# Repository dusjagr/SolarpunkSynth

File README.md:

# SolarpunkSynth 🌞🎹

A solar-powered synthesizer that creates experimental sounds, rhythmic patterns, and beats using minimal energy from the sun! This project embodies the spirit of solarpunk by combining sustainable energy with creative expression.

# Workshop Registration
https://sgmkcloud.ocloud.de/index.php/apps/forms/65qHgGpafZMqBaDL

## Description

The SolarpunkSynth is an ultra-low power consumption synthesizer that can be powered by:
- Silicon solar cells
- DIY DSSC (Dye-sensitized solar cells)
- Alternative power sources (mud batteries, potato power, coconut energy)
- Nearly depleted batteries (due to extremely low power requirements)

## Project Variants

This repository contains two versions of the SolarpunkSynth:

### 1. Original SolarpunkSynth
Located in [`/SolarPunkSynth`](./SolarPunkSynth)
- The original version of the solar-powered synthesizer
- Simple and elegant design
- Perfect for beginners and workshops
- Includes complete documentation and assembly instructions

### 2. Digilog Edition
Located in [`/SolarSynth_digilog`](./SolarSynth_digilog)
- Enhanced version with digital-inspired aesthetics
- Developed for the Digilog exhibition in Taipei, Taiwan
- Features artistic PCB design with custom graphics
- Same core functionality with a unique visual style

## Technical Details

The synthesizer is built around these key features:
- Based on hex-inverter chip (74HC14)
- Three interdependent oscillators coupled through piezo discs
- Ultra-low energy consumption (<0.5mA)
- Audio output via 3.5mm jack
- Organic, variable rhythms through unstable circuit states
- KiCad PCB design files included

### Technical Differences Between Variants

#### Original SolarpunkSynth
- Simple and robust circuit design
- Direct audio output from oscillator circuit
- Basic component selection for easy assembly
- Standard PCB layout optimized for functionality
- Ideal for workshops and educational purposes

#### Digilog Edition Enhancements
- Added MCP6002 dual op-amp for improved audio output buffering
- Enhanced signal conditioning with additional filtering capacitors
- Modified component values for better stability
- Custom footprint library optimized for artistic PCB layout
- Artistic PCB design with custom traces and visual elements
- ENIG finish recommended for superior aesthetic presentation
- Optional acrylic cover design for finished look and protection

### Schematic

You can also view the [minimal schematic as PDF](./SolarPunkSynth/instructions/DSSC_Synthminimal_schema.pdf).

## Assembly Instructions

### Original SolarpunkSynth

For the original SolarpunkSynth version:
- [Detailed Soldering Guide (PDF)](./SolarPunkSynth/instructions/SolderInstruction.pdf)
- [Soldering Guide (SVG)](./SolarPunkSynth/instructions/SolderInstruction.svg)
- **[Complete step-by-step assembly instructions](./SolarPunkSynth/README.md#detailed-step-by-step-assembly-instructions)** are included in the SolarPunkSynth README.md

### Digilog Edition

Instruction photos are available:

For the Digilog edition, additional documentation is available:
- [Leaflet Format Instructions (PDF)](./SolarSynth_digilog/instructions/SolarpunkSynth_SolderInstruction_leaflet.pdf)
- [Inside Pages (PDF)](./SolarSynth_digilog/instructions/SolarpunkSynth_SolderInstruction_leaflet_inside.pdf)
- [Outside Pages (PDF)](./SolarSynth_digilog/instructions/SolarpunkSynth_SolderInstruction_leaflet_outside.pdf)

## Repository Contents

- [`/SolarPunkSynth`](./SolarPunkSynth) - Original version KiCad files and documentation
  - [`/002_SolarPunkSynth_footprints.pretty`](./SolarPunkSynth/002_SolarPunkSynth_footprints.pretty) - Custom footprints for the PCB
  - [`/MASK`](./SolarPunkSynth/MASK) - PCB mask files and design assets
  - [`/instructions`](./SolarPunkSynth/instructions) - Assembly guides and schematics
  - [`/svg2shenzhen`](./SolarPunkSynth/svg2shenzhen) - SVG files for PCB artwork

- [`/SolarSynth_digilog`](./SolarSynth_digilog) - Digilog edition KiCad files
  - [`/3d_models`](./SolarSynth_digilog/3d_models) - 3D models of components
  - [`/DIY_pcb`](./SolarSynth_digilog/DIY_pcb) - DIY PCB patterns and masks for custom fabrication
  - [`/acrylicCover_digilog`](./SolarSynth_digilog/acrylicCover_digilog) - Design files for the optional acrylic protective cover
  - [`/gerber`](./SolarSynth_digilog/gerber) - Manufacturing files
  - [`/instructions`](./SolarSynth_digilog/instructions) - Enhanced assembly guides in multiple formats
  - [`/svg2shenzhen`](./SolarSynth_digilog/svg2shenzhen) - Custom PCB artwork files
  - [`BOM.ods`](./SolarSynth_digilog/BOM.ods) - Detailed bill of materials in OpenDocument Spreadsheet format

- [`/photos`](./photos) - Project photos and workshop documentation

## DIY PCB Fabrication

For those interested in creating their own PCBs at home or in makerspaces, the Digilog edition includes DIY PCB files:
- [`SolarSynth_MASK.png`](./SolarSynth_digilog/DIY_pcb/SolarSynth_MASK.png) - Printable mask pattern for toner transfer or photolithography
- [`SolarSynth_digilog_MASK.svg`](./SolarSynth_digilog/DIY_pcb/SolarSynth_digilog_MASK.svg) - Vector version of the mask for scaling and modifications

These files can be used with common DIY PCB fabrication methods like toner transfer, photolithography, or CNC milling.

## Acrylic Cover

The Digilog edition offers an optional aesthetic acrylic cover:
- [`acrylCover_digilog.dxf`](./SolarSynth_digilog/acrylicCover_digilog/acrylCover_digilog.dxf) - CAD file for laser cutting
- [`drawing.svg`](./SolarSynth_digilog/acrylicCover_digilog/drawing.svg) - Vector drawing for preview and modifications

The acrylic cover enhances the visual appeal while providing protection to the electronics.

## Workshop Information

A solar-powered synthesizer that creates experimental sounds, rhythmic patterns, and beats using minimal energy from the sun! This project embodies the spirit of solarpunk by combining sustainable energy with creative expression.

<figure>
  
  <figcaption><em>Impressions from the workshop at digilog, Taipei, February 2025</em></figcaption>
</figure>

This project is designed to be beginner-friendly and has been successfully taught in workshops across various locations including:
- Taipei, Taiwan (Digilog)
- Chiang Mai, Thailand
- Tokyo, Japan (FabCafe)

No prior electronics knowledge is required - just enthusiasm for experimental sounds and solar-powered creativity!

<figure>
  
  <figcaption><em>Photos from the SolarpunkSynth Workshop at Parang Cafe & Art Stay, Chiang Mai, Thailand</em></figcaption>
</figure>

## Credits

This circuit is a modified version of the StarvationSynth originally developed by Ralf Schreiber and Uwe Schüler. The current version was specifically developed by Marc Dusseiller (dusjagr) to support the exhibition "1,540,000nm DSSC" by Shih Wei-Chieh at FabCafe Tokyo.

### Tools Used
- [svg2shenzhen](https://github.com/badgeek/svg2shenzhen) - An Inkscape extension that converts SVG drawings to KiCad PCB layouts, allowing for artistic and unrestricted PCB designs with support for any kind of shapes, drill pads, and edge cuts. Special thanks to Budi Prakosa ([@badgeek](https://github.com/badgeek)) for creating this amazing tool!
- KiCad - PCB design software

## Links

- [Project Wiki](https://www.hackteria.org/wiki/SolarpunkSynth)
- [Hackteria Network](http://hackteria.org/)
- [SGMK](https://mechatronicart.ch/)
- [Bitwäscherei Hackerspace](https://bitwaescherei.ch/)

## License

This project is open hardware - feel free to modify and share!

This project is licensed under the CERN Open Hardware License Version 2 - Permissive (CERN-OHL-P v2). This means you are free to:
- Study
- Modify
- Make
- Distribute

without any obligation to share your changes or modifications.

For more details, see the [LICENSE](./LICENSE) file.

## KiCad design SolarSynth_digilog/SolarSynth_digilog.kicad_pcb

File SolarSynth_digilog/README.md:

# SolarpunkSynth Digilog Edition

This is the Digilog edition of the SolarpunkSynth, specially developed for the Digilog exhibition in Taipei, Taiwan. This version features an artistic PCB design while maintaining the core functionality of the original SolarpunkSynth.

## Features
- Enhanced PCB design with digital-inspired aesthetics
- Artistic circuit traces and visual elements
- Exhibition-ready presentation
- Improved audio output stage with op-amp buffer
- Ultra-low power consumption (<0.5mA)

## Technical Enhancements
- Added MCP6002 dual op-amp for better audio output buffering
- Enhanced signal conditioning with additional filtering
- Modified component values for improved stability
- Custom footprint library optimized for artistic PCB layout
- Polarized capacitors for better power filtering

## Directory Contents
- `/3d_models/` - 3D models of components for visualization
- `/gerber/` - Manufacturing files for PCB production
- `/svg2shenzhen/` - Custom PCB artwork files

## Exhibition History
- Digilog Exhibition, Taipei, Taiwan
- Part of the exploration of digital aesthetics in analog circuits
- Demonstrates the intersection of art and technology

## Technical Specifications
- Based on 74HC14 hex-inverter chip
- Three coupled oscillators using piezo discs
- MCP6002 dual op-amp for audio buffering
- Solar-powered operation
- 3.5mm audio output
- Artistic PCB design with custom traces

## PCB Design Process
The artistic PCB design was created using:
- [svg2shenzhen](https://github.com/badgeek/svg2shenzhen) - An Inkscape extension that transforms SVG artwork into KiCad PCB layouts, enabling complete creative freedom in PCB design with support for any shape and custom drill sizes
- Custom artwork designed specifically for the Digilog exhibition
- Careful consideration of both aesthetic and functional aspects

## Manufacturing Notes
- Gerber files are provided in the `/gerber/` directory
- PCB specifications:
  - 2-layer board
  - Custom silkscreen artwork
  - ENIG finish recommended for best aesthetic results

## Assembly
While the assembly process is similar to the original SolarpunkSynth, this version includes additional components:
1. MCP6002 dual op-amp in DFN-8 package
2. Additional filtering capacitors
3. Modified resistor values for the op-amp stage

Please refer to the schematic for detailed component values and connections.

## License
This project is licensed under the CERN Open Hardware License Version 2 - Permissive (CERN-OHL-P v2).

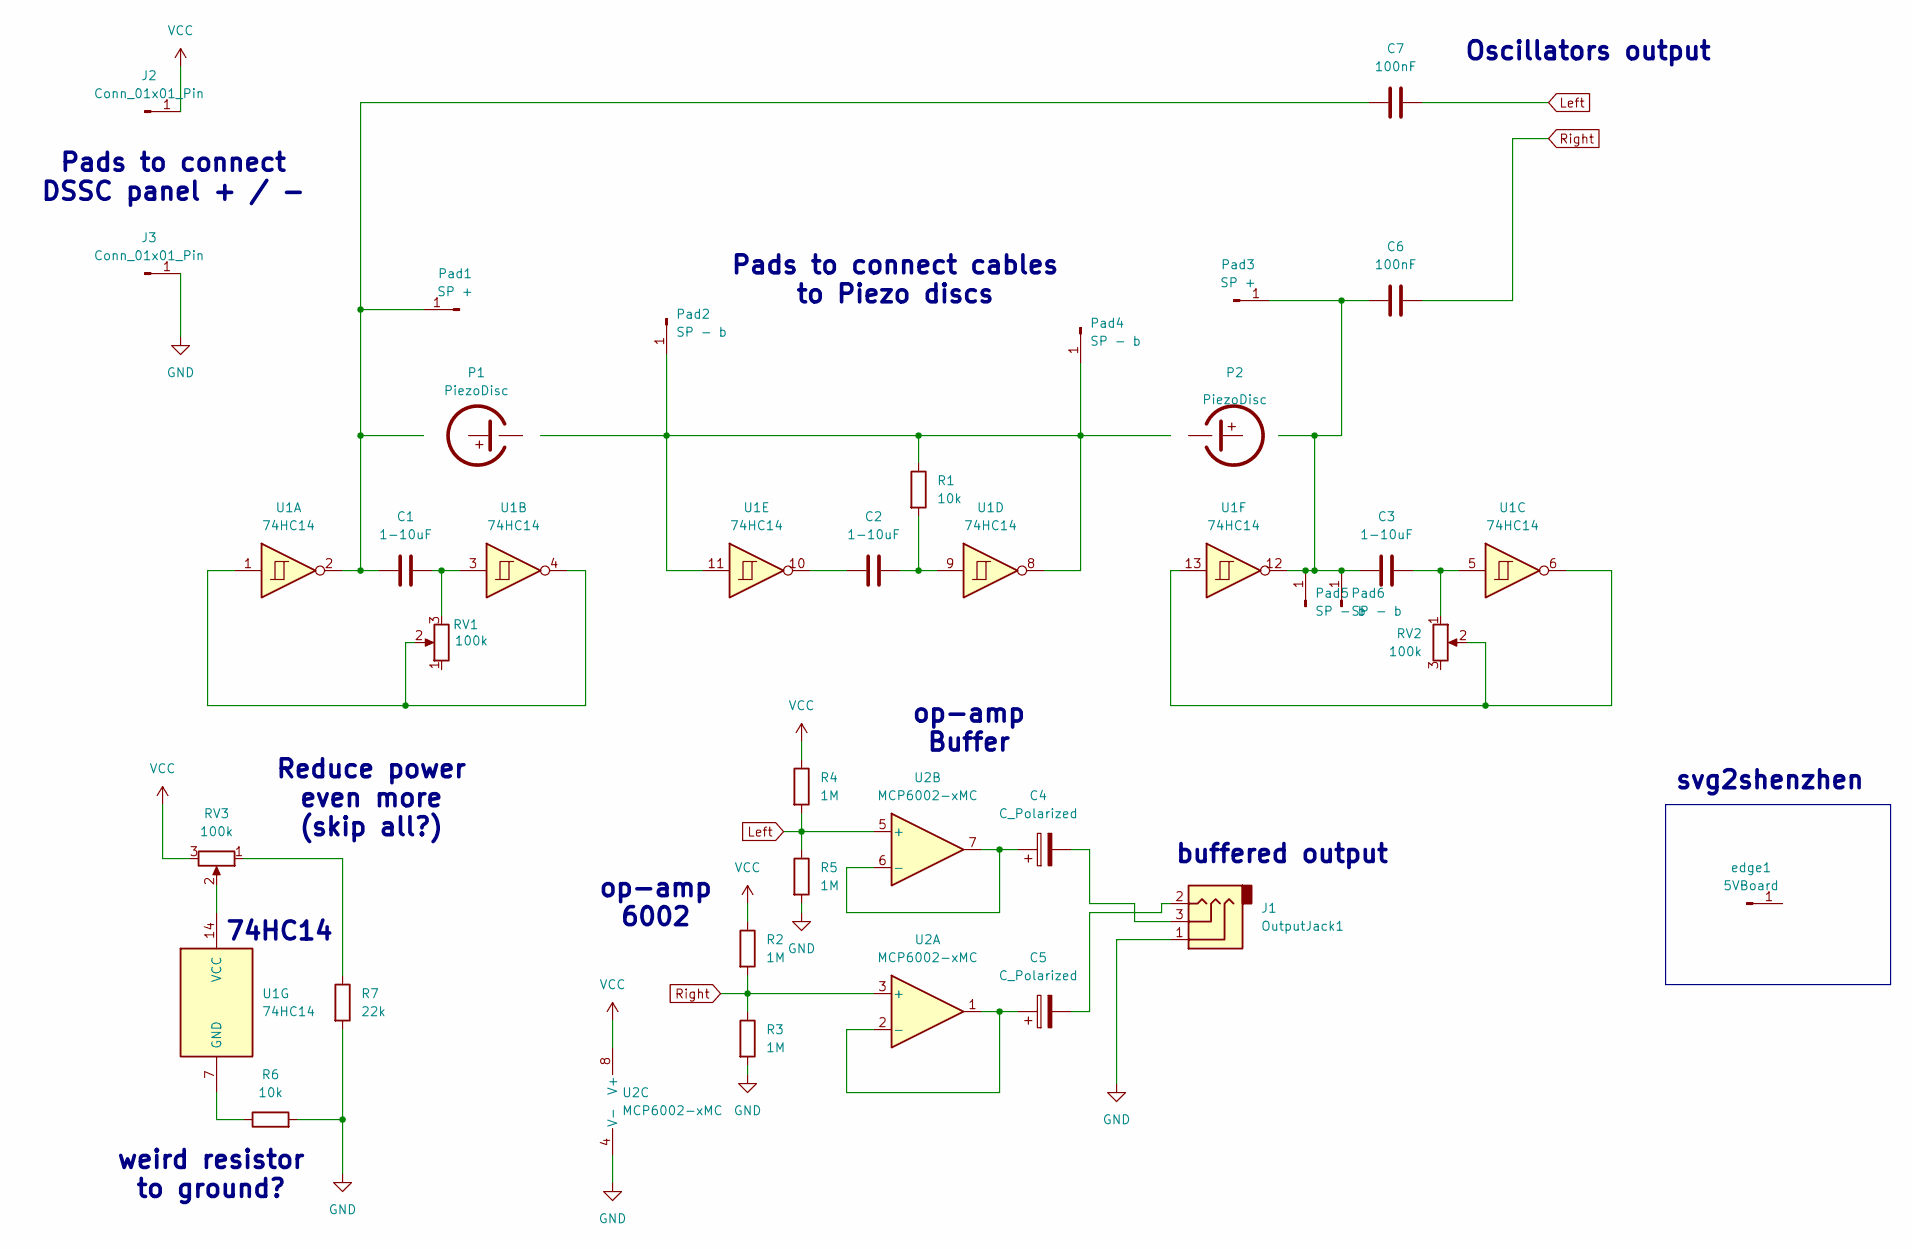
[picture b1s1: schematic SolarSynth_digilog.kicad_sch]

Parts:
C1, C2, C3: 1-10uF; C_1210_noGND
C4, C5: C_Polarized; C_1210_noGND
C6, C7: 100nF; C_1210_noGND
J1: OutputJack1; AUDIO-JACK-3.5mm_SMD_noHole
J2, J3: Conn_01x01_Pin; SolarPad_VCC
P1, P2: PiezoDisc; Piezo_20mm
Pad1, Pad3: SP +; SolderPad_small
Pad2, Pad4, Pad5, Pad6: SP - b; SolderPad_small
R1, R6: 10k; R_1206_noGND
R2, R3, R4, R5: 1M; R_1206_noGND
R7: 22k; R_1206_noGND
RV1, RV2: 100k; RD901F-ALPHA-3D_minis
RV3: 100k; RD901F-ALPHA-3D_longpads
U1: 74HC14; DIP-14_W7.62mm_LongerPads
U2: MCP6002-xMC; DIP-8_W7.62mm_LongerPads
edge1: 5VBoard; board_digilog

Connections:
GND: J1.1, J3.1, R3.2, R5.2, R6.2, R7.2, U2.4 (V-), U2.9 (V-)
Left: C7.2, R4.2, R5.1, U2.5 (+)
unnamed: C1.2, RV1.3, U1.3
unnamed: C2.1, U1.10
unnamed: C2.2, R1.2, U1.9
unnamed: C3.2, RV2.1, U1.5
unnamed: C4.2, J1.3
unnamed: C5.2, J1.2
unnamed: C1.1, C7.1, Pad1.1, U1.2
unnamed: Pad2.1, Pad4.1, R1.1, U1.8, U1.11
unnamed: C3.1, C6.1, Pad3.1, Pad5.1, Pad6.1, U1.12
unnamed: R7.1, RV3.1
unnamed: RV1.2, U1.1, U1.4
unnamed: RV2.2, U1.6, U1.13
unnamed: R6.1, U1.7 (GND)
unnamed: RV3.2, U1.14 (VCC)
unnamed: C5.1, U2.1, U2.2 (-)
unnamed: C4.1, U2.6 (-), U2.7
Right: C6.2, R2.2, R3.1, U2.3 (+)
VCC: J2.1, R2.1, R4.1, RV3.3, U2.8 (V+)

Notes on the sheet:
svg2shenzhen
Pads to connect cables to Piezo discs
Oscillators output
Reduce power even more (skip all?)
op-amp Buffer
op-amp 6002
weird resistor to ground?
74HC14
buffered output
Pads to connect DSSC panel + / -

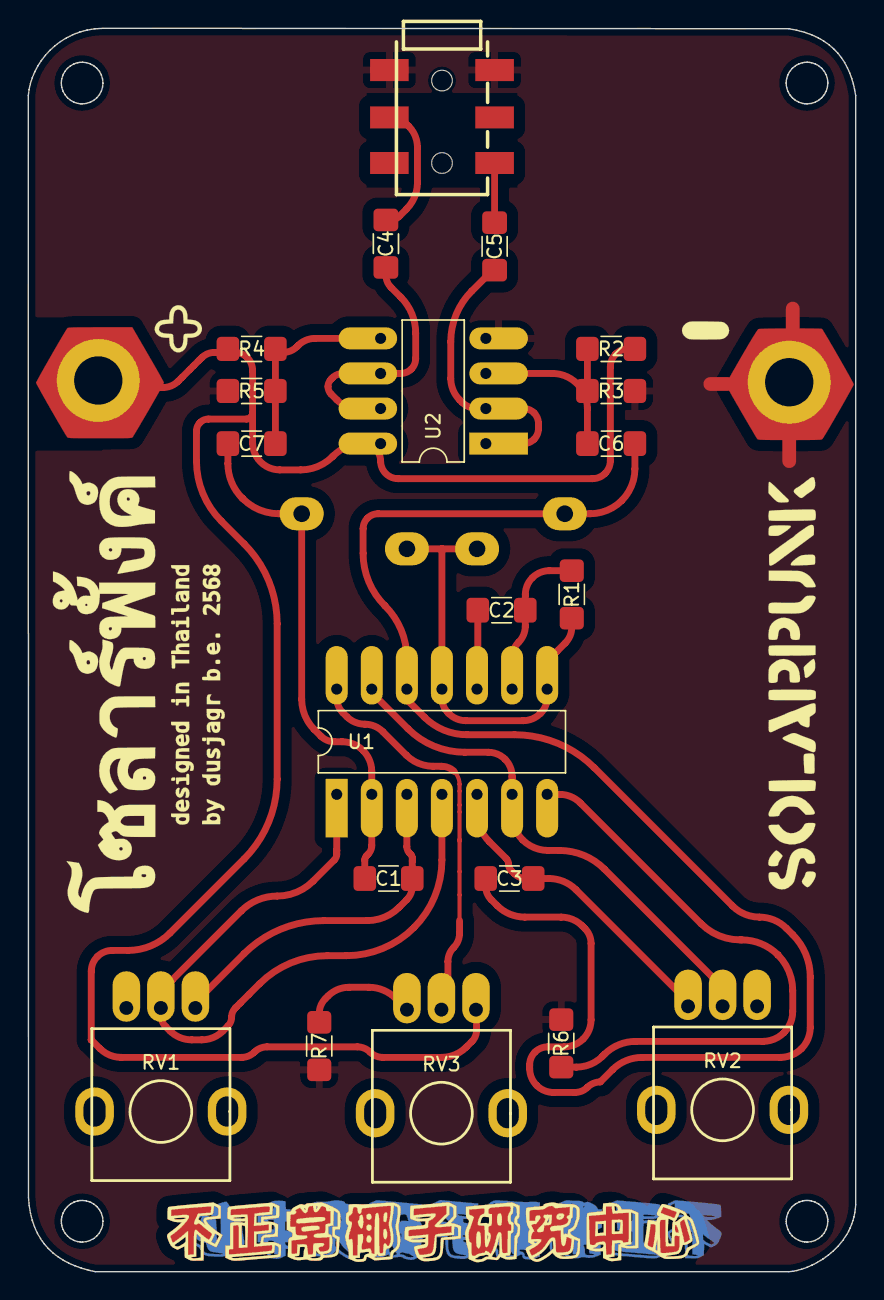
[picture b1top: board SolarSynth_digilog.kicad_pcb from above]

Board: 2 copper layers, 59.9 x 90.0 mm, 31 parts (1 on the bottom side), 20 nets.

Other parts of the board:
Ref**: Val**; graphix_digilog
Ref**#2: Val**; back_graphix_digilog

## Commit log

2025-02-12 first commit both synth boards
2025-02-12 Add .gitignore for KiCad project
2025-02-12 Remove build outputs from .gitignore
2025-02-12 Update README with comprehensive project information
2025-02-12 Add images and assembly instructions to README
2025-02-12 Fix schema display in README by using jpg instead of pdf
2025-02-12 Add workshop and finished product photos
2025-02-12 Fix image paths in README to use relative paths
2025-02-12 Add directory links to Repository Contents section
2025-02-12 Update KiCad project files and add 3D models
2025-02-12 Update .gitignore with comprehensive KiCad ignore patterns and remove tracked cache files
2025-02-12 Remove KiCad backup directory from Git tracking
2025-02-12 Update to CERN Open Hardware License Version 2 - Permissive
2025-02-12 Add Digilog variant photo
2025-02-12 Scale images to consistent width in README
2025-02-12 Add specific README files for both SolarpunkSynth variants
2025-02-12 Update READMEs with technical differences between variants
2025-02-12 Add photos to variant READMEs - Workshop experience and finished product photos
2025-02-12 Update svg2shenzhen description with more detailed information
2025-02-12 Add thanks to svg2shenzhen author Budi Prakosa
2025-03-11 Update documentation with detailed assembly instructions and add new resources for Digilog edition
2025-03-12 Add workshop photos and update README with image captions
2025-03-15 Update README.md
    added registration form
